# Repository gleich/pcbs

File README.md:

# pcbs

printed circuit board designs I've made

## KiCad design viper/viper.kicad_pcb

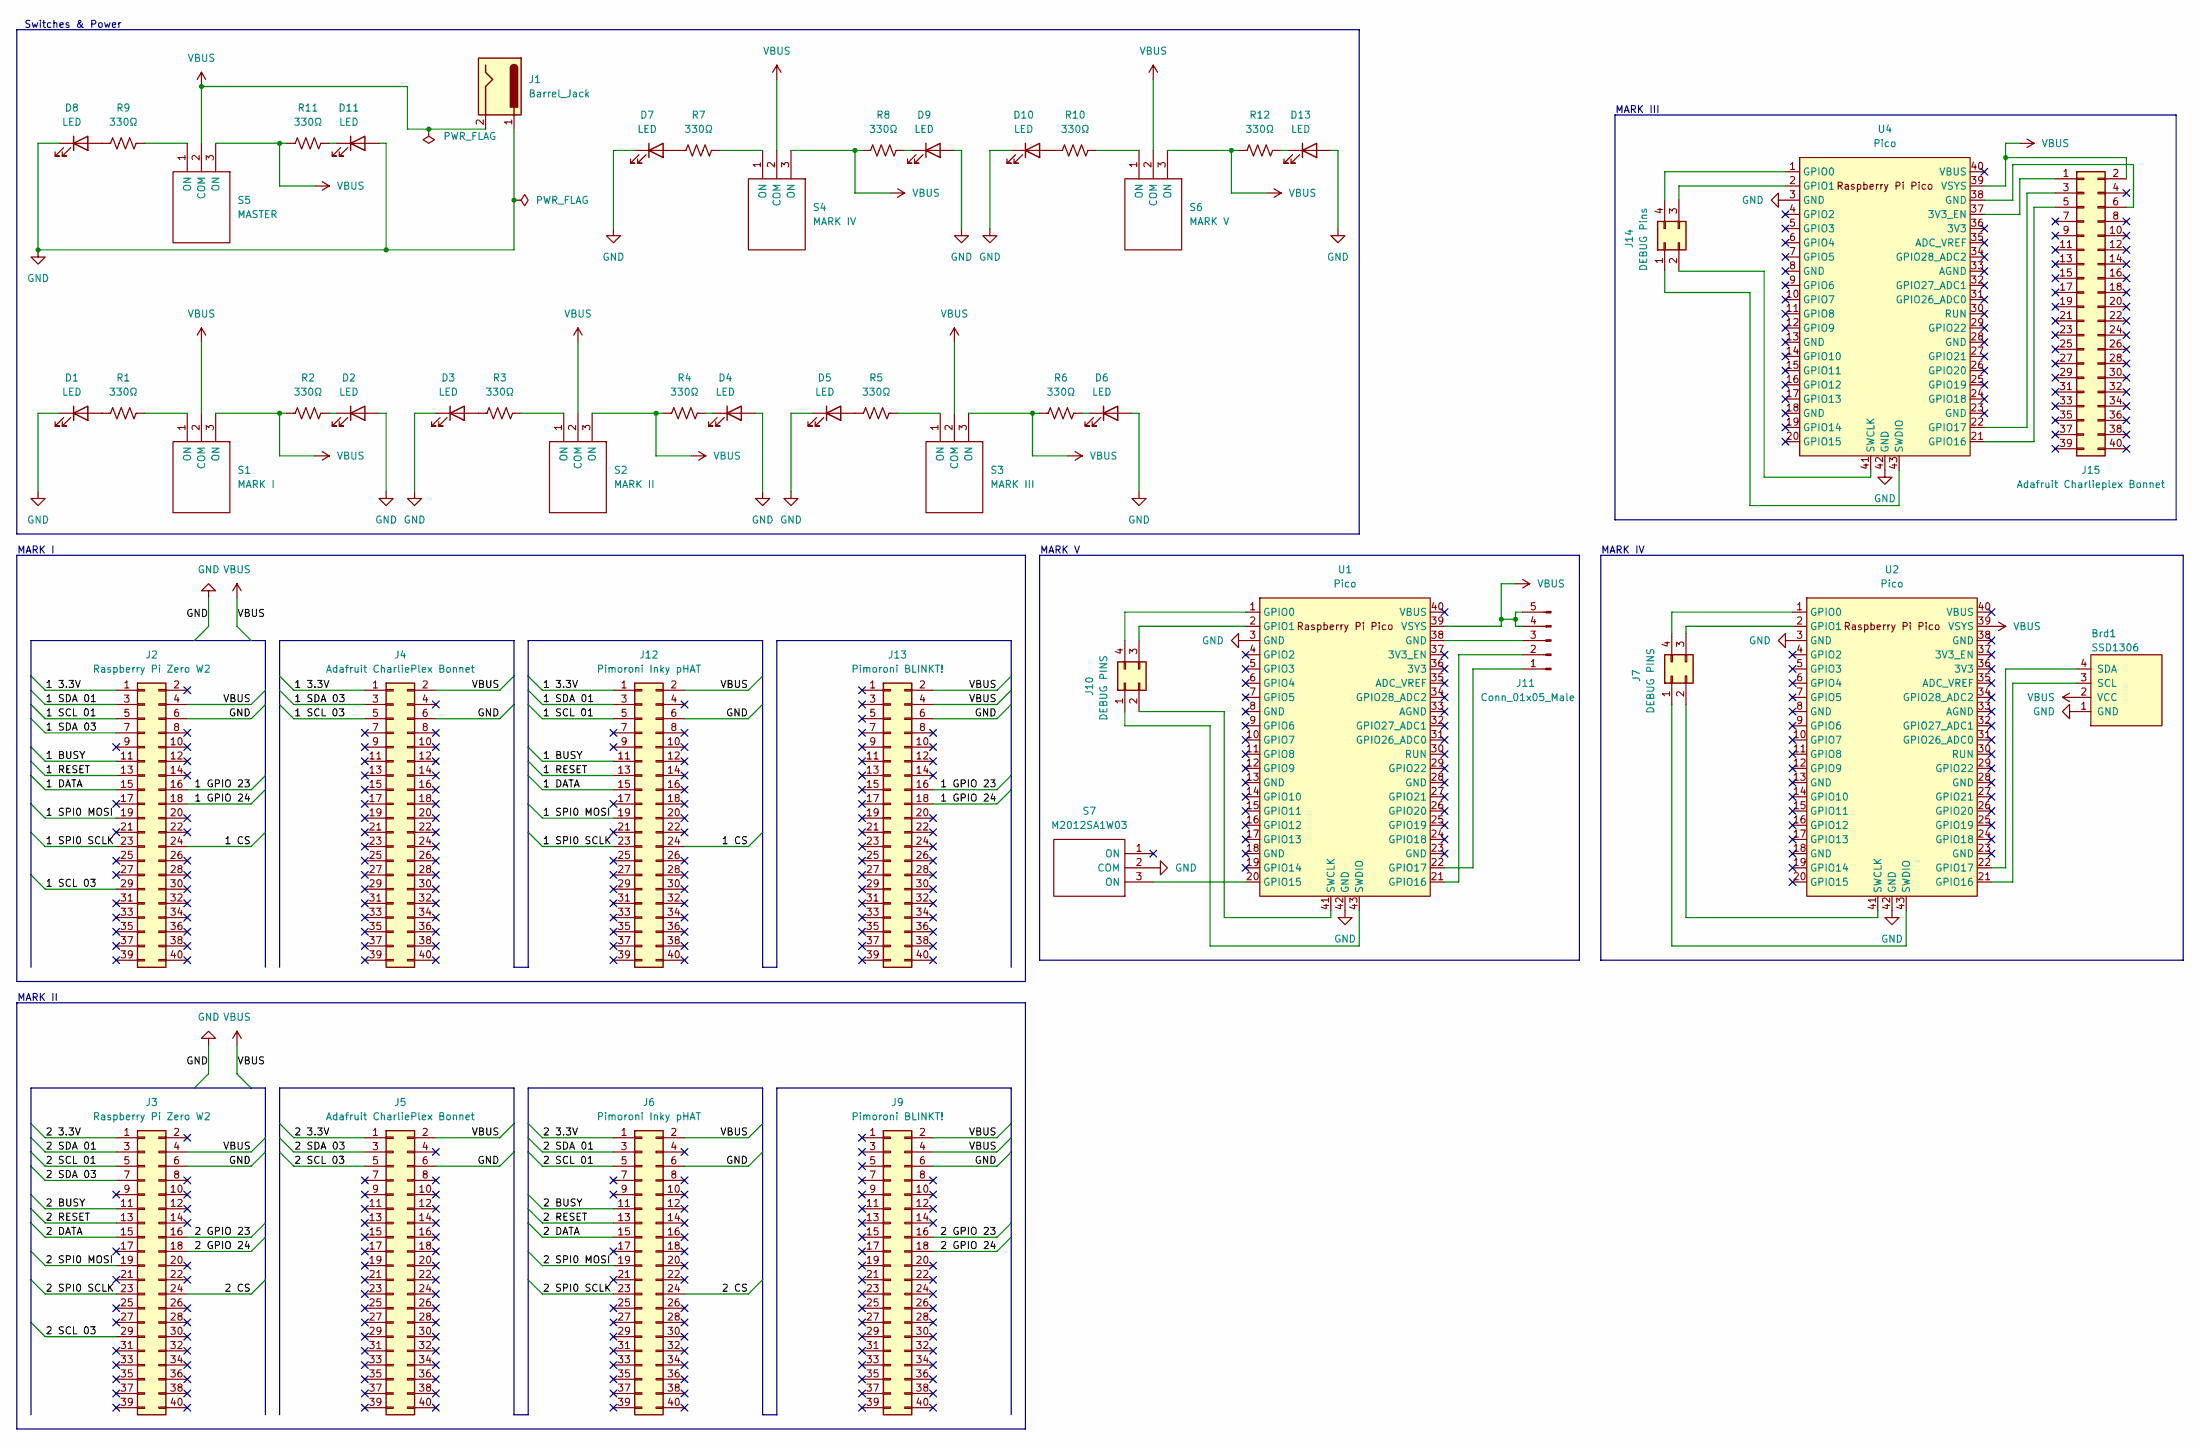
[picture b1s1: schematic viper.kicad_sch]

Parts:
Brd1: SSD1306; 128x64OLED
D1, D2, D3, D4, D5, D6, D7, D8, D9, D10, D11, D13: LED; LED_D5.0mm
J1: Barrel_Jack; BarrelJack_Wuerth_6941xx301002
J2, J3: Raspberry Pi Zero W2; PinHeader_2x20_P2.54mm_Vertical
J4, J5: Adafruit CharliePlex Bonnet; PinHeader_2x20_P2.54mm_Vertical
J6, J12: Pimoroni Inky pHAT; PinHeader_2x20_P2.54mm_Vertical
J7, J10: DEBUG PINS; PinHeader_2x02_P2.54mm_Vertical
J9, J13: Pimoroni BLINKT!; PinHeader_2x20_P2.54mm_Vertical
J11: Conn_01x05_Male; PinHeader_1x05_P2.54mm_Vertical
J14: DEBUG Pins; PinHeader_2x02_P2.54mm_Vertical
J15: Adafruit Charlieplex Bonnet; PinHeader_2x20_P2.54mm_Vertical
R1, R2, R3, R4, R5, R6, R7, R8, R9, R10, R11, R12: 330Ω; R_Axial_DIN0309_L9.0mm_D3.2mm_P12.70mm_Horizontal
S1: MARK I; M2012SA1W03; Manufacturer_Part_Number M2012SA1W03; Mouser Part Number 633-M2012A03
S2: MARK II; M2012SA1W03; Manufacturer_Part_Number M2012SA1W03; Mouser Part Number 633-M2012A03
S3: MARK III; M2012SA1W03; Manufacturer_Part_Number M2012SA1W03; Mouser Part Number 633-M2012A03
S4: MARK IV; M2012SA1W03; Manufacturer_Part_Number M2012SA1W03; Mouser Part Number 633-M2012A03
S5: MASTER; M2012SA1W03; Manufacturer_Part_Number M2012SA1W03; Mouser Part Number 633-M2012A03
S6: MARK V; M2012SA1W03; Manufacturer_Part_Number M2012SA1W03; Mouser Part Number 633-M2012A03
S7: M2012SA1W03; Manufacturer_Part_Number M2012SA1W03; Mouser Part Number 633-M2012A03
U1, U2, U4: Pico; RPi_Pico_SMD_TH

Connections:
/1 3.3V: J2.1, J4.1, J12.1
/1 BUSY: J2.11, J12.11
/1 CS: J2.24, J12.24
/1 DATA: J2.15, J12.15
/1 GPIO 23: J2.16, J13.16
/1 GPIO 24: J2.18, J13.18
/1 RESET: J2.13, J12.13
/1 SCL 01: J2.5, J12.5
/1 SCL 03: J2.29, J4.5
/1 SDA 01: J2.3, J12.3
/1 SDA 03: J2.7, J4.3
/1 SPI0 MOSI: J2.19, J12.19
/1 SPI0 SCLK: J2.23, J12.23
/2 3.3V: J3.1, J5.1, J6.1
/2 BUSY: J3.11, J6.11
/2 CS: J3.24, J6.24
/2 DATA: J3.15, J6.15
/2 GPIO 23: J3.16, J9.16
/2 GPIO 24: J3.18, J9.18
/2 RESET: J3.13, J6.13
/2 SCL 01: J3.5, J6.5
/2 SCL 03: J3.29, J5.5
/2 SDA 01: J3.3, J6.3
/2 SDA 03: J3.7, J5.3
/2 SPI0 MOSI: J3.19, J6.19
/2 SPI0 SCLK: J3.23, J6.23
GND: Brd1.1 (GND), D1.1 (K), D2.2 (A), D3.1 (K), D4.2 (A), D5.1 (K), D6.2 (A), D7.1 (K), D8.1 (K), D9.2 (A), D10.1 (K), D11.2 (A), D13.2 (A), J1.1, J2.6, J3.6, J4.6, J5.6, J6.6, J9.6, J12.6, J13.6, S7.2 (COM), U1.3 (GND), U1.42 (GND), U2.3 (GND), U2.42 (GND), U4.3 (GND), U4.42 (GND)
unnamed: Brd1.3 (SCL), U2.21 (GPIO16)
unnamed: Brd1.4 (SDA), U2.22 (GPIO17)
unnamed: D1.2 (A), R1.1
unnamed: D2.1 (K), R2.2
unnamed: D3.2 (A), R3.1
unnamed: D4.1 (K), R4.2
unnamed: D5.2 (A), R5.1
unnamed: D6.1 (K), R6.2
unnamed: D7.2 (A), R7.1
unnamed: D8.2 (A), R9.1
unnamed: D9.1 (K), R8.2
unnamed: D10.2 (A), R10.1
unnamed: D11.1 (K), R11.2
unnamed: D13.1 (K), R12.2
unnamed: J7.1, U2.43 (SWDIO)
unnamed: J7.2, U2.41 (SWCLK)
unnamed: J7.3, U2.2 (GPIO1)
unnamed: J7.4, U2.1 (GPIO0)
unnamed: J10.1, U1.43 (SWDIO)
unnamed: J10.2, U1.41 (SWCLK)
unnamed: J10.3, U1.2 (GPIO1)
unnamed: J10.4, U1.1 (GPIO0)
unnamed: J11.1, U1.22 (GPIO17)
unnamed: J11.2, U1.21 (GPIO16)
unnamed: J11.3, U1.38 (GND)
unnamed: J14.1, U4.43 (SWDIO)
unnamed: J14.2, U4.41 (SWCLK)
unnamed: J14.3, U4.2 (GPIO1)
unnamed: J14.4, U4.1 (GPIO0)
unnamed: J15.1, U4.37 (3V3_EN)
unnamed: J15.3, U4.22 (GPIO17)
unnamed: J15.5, U4.21 (GPIO16)
unnamed: J15.6, U4.38 (GND)
unnamed: R1.2, S1.1 (ON)
unnamed: R3.2, S2.1 (ON)
unnamed: R5.2, S3.1 (ON)
unnamed: R7.2, S4.1 (ON)
unnamed: R9.2, S5.1 (ON)
unnamed: R10.2, S6.1 (ON)
unnamed: S7.3 (ON), U1.20 (GPIO15)
VBUS: Brd1.2 (VCC), J1.2, J2.4, J3.4, J4.2, J5.2, J6.2, J9.2, J9.4, J11.4, J11.5, J12.2, J13.2, J13.4, J15.2, R2.1, R4.1, R6.1, R8.1, R11.1, R12.1, S1.2 (COM), S1.3 (ON), S2.2 (COM), S2.3 (ON), S3.2 (COM), S3.3 (ON), S4.2 (COM), S4.3 (ON), S5.2 (COM), S5.3 (ON), S6.2 (COM), S6.3 (ON), U1.39 (VSYS), U2.39 (VSYS), U4.39 (VSYS)

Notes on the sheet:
MARK IV
Switches & Power
MARK II
MARK V
MARK I
MARK III

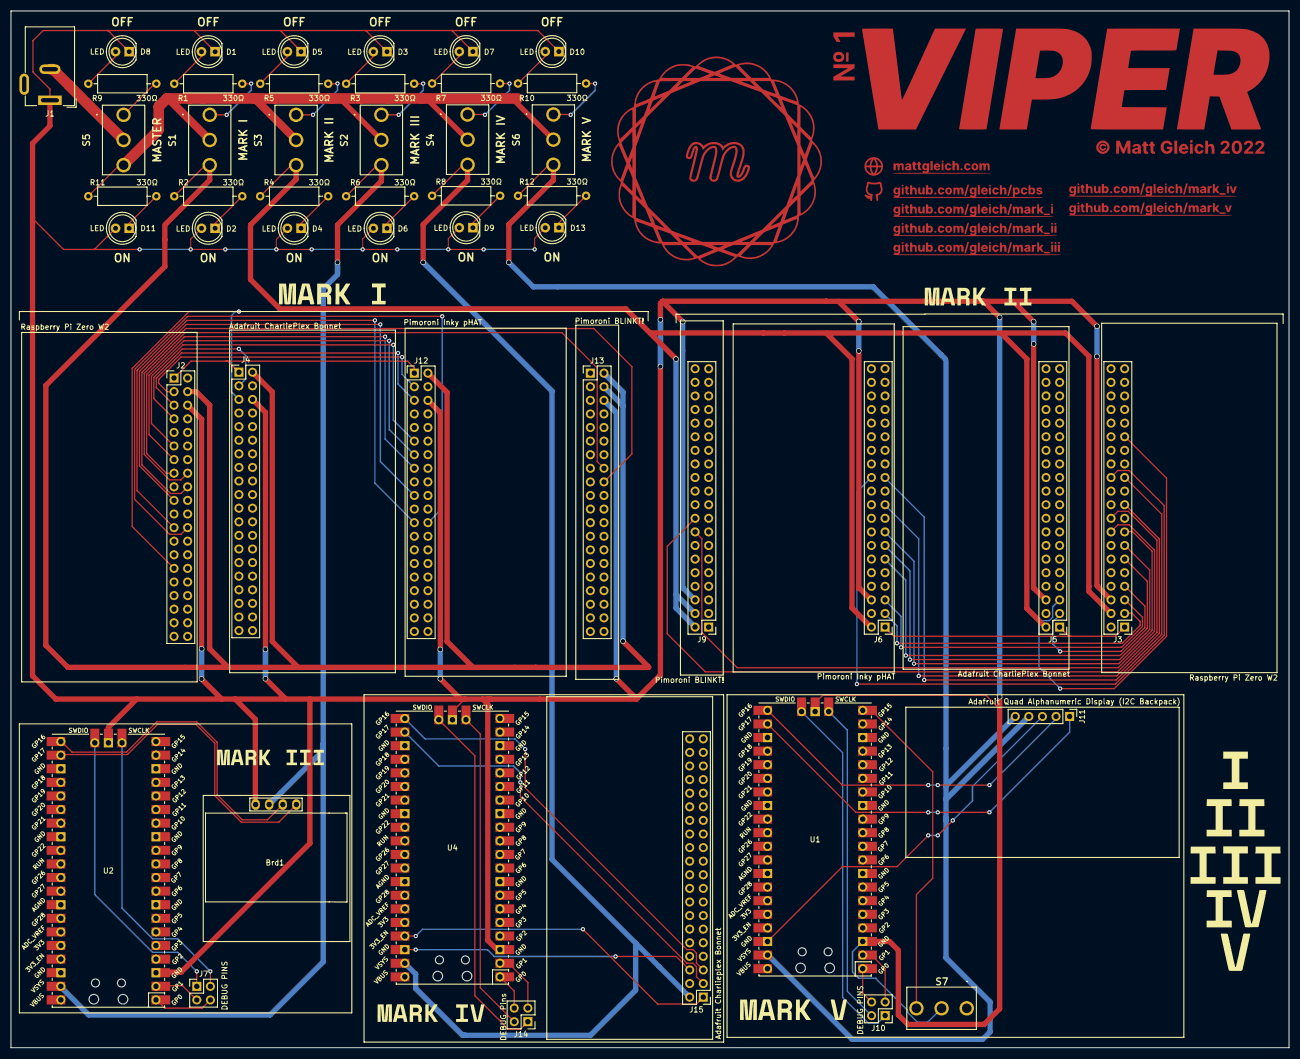
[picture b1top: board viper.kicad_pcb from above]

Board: 2 copper layers, 238.8 x 193.7 mm, 49 parts (0 on the bottom side), 68 nets.

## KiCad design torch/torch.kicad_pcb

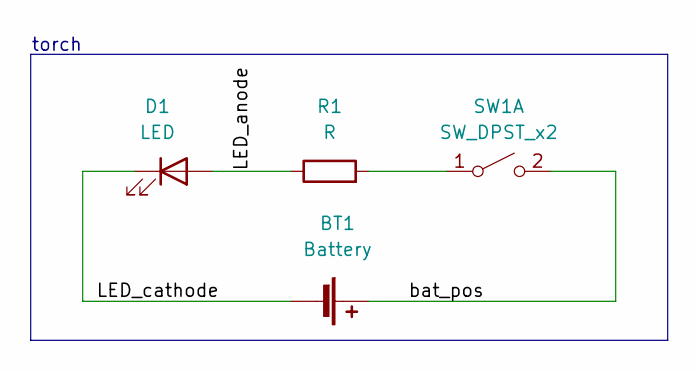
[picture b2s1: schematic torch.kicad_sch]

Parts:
BT1: Battery; BatteryHolder_Keystone_1058_1x2032
D1: LED; LED_D5.0mm
R1: R; R_Axial_DIN0204_L3.6mm_D1.6mm_P7.62mm_Horizontal
SW1: SW_DPST_x2; SW_TH_Tactile_Omron_B3F-10xx

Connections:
/LED_anode: D1.2 (A), R1.1
/LED_cathode: BT1.2 (-), D1.1 (K)
/bat_pos: BT1.1 (+), SW1.2 (B)
unnamed: R1.2, SW1.1 (A)

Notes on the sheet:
torch

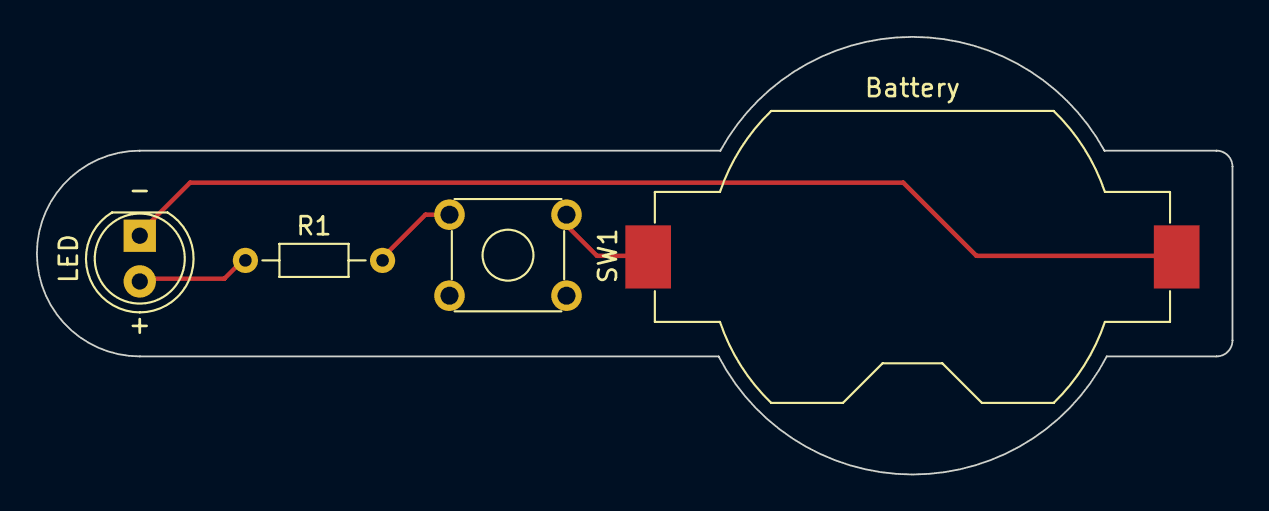
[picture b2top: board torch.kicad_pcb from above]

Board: 2 copper layers, 66.4 x 24.3 mm, 5 parts (1 on the bottom side), 4 nets.

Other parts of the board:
logo: LOGO; logo

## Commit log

2021-12-08 feat: init ghs_series pcb
2021-12-08 feat: add linguist detection
2021-12-08 docs: add README.md
2021-12-08 feat: basic design
2021-12-08 feat: remove .DS_Store
2021-12-08 feat: ignore fp-info-cache
2021-12-10 feat: adjust sizing and values
2022-02-05 feat: reset
2022-02-05 chore(config): have all kicad files be detected linguist
2022-02-05 feat: init torch project
2022-02-05 feat: schematic
2022-02-10 feat: base PCB rectangle
2022-02-10 feat: wire footprints
2022-02-10 feat: add arcs
2022-02-10 feat: silkscreen
2022-02-10 feat: gerbers
2022-02-10 chore(config): ignore zip files
2022-02-10 feat: center resistor
2022-02-11 feat: dimensions
2022-02-12 feat: align items
2022-02-16 feat: init streets
2022-02-21 feat: refactor to use bus
2022-03-10 feat: setup proper bus from pi
2022-03-10 feat: full board
2022-03-29 feat: init viper
2022-03-29 feat: setup viper sch
2022-03-29 feat: switches and power
2022-03-30 feat: pcbs and MARK I and MARK II
2022-04-05 feat: mark IV and V
2022-04-10 feat: assign footprints
    verification still needed
2022-04-10 chore: align items on board
2022-04-13 feat: correct footprints and start PCB
2022-04-13 feat: off switch routing
2022-04-13 feat: switch routing
2022-04-19 feat: improve arrangement
2022-04-24 feat: switches
2022-04-24 feat: align switches
2022-04-24 feat: route switches
2022-04-27 feat: mark i
2022-04-27 feat: mark ii routing
2022-04-27 feat: graphics
2022-04-28 feat: final connections
2022-05-18 feat: fixes
2022-06-02 feat: final viper board changes

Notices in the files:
torch/torch.kicad_pcb:
© Matt Gleich 2022
